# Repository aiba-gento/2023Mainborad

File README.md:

# 2023Mainborad
2023年ロボコン用マザーボード

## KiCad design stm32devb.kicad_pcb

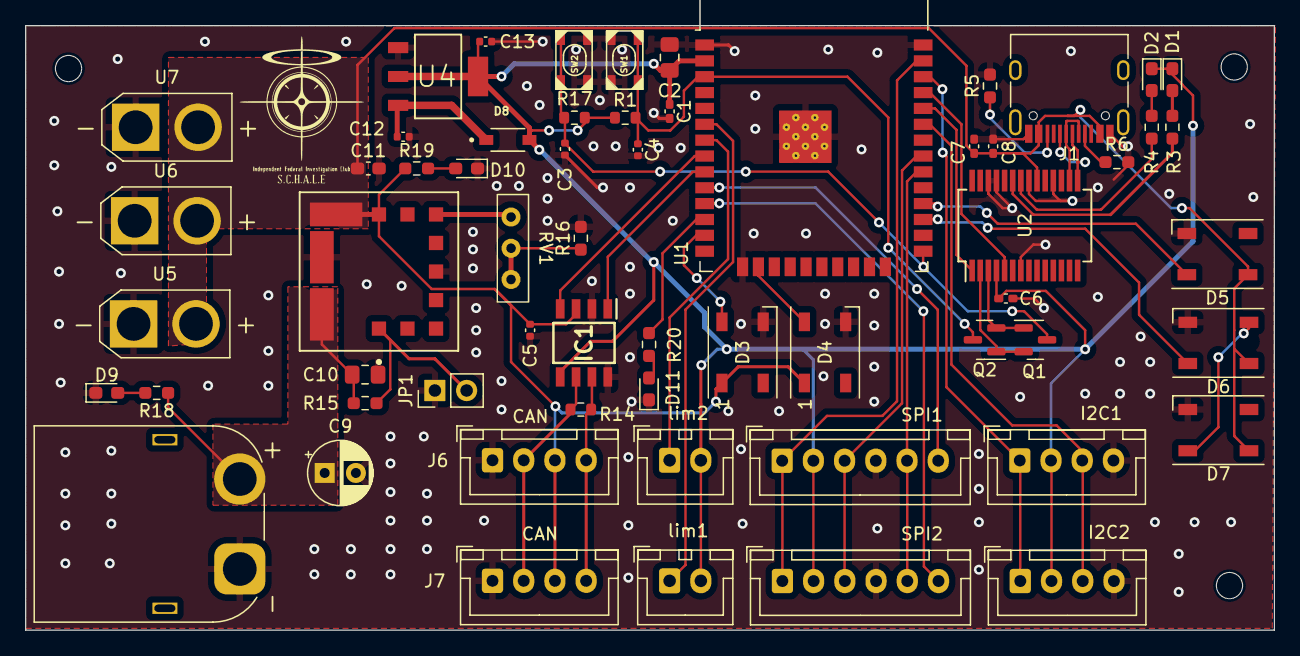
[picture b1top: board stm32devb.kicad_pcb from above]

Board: 2 copper layers, 100.0 x 48.4 mm, 60 parts (0 on the bottom side), 44 nets.

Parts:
C1, C6, C7: 0.1u; C_0402_1005Metric_Pad0.74x0.62mm_HandSolder
C2, C10: 22u; C_0805_2012Metric_Pad1.18x1.45mm_HandSolder
C3, C4, C5: 0.1u; C_0402_1005Metric
C8: 4.7u; C_0402_1005Metric_Pad0.74x0.62mm_HandSolder
C9: 220u; CP_Radial_D5.0mm_P2.50mm
C11: 10u; C_0603_1608Metric_Pad1.08x0.95mm_HandSolder
C12, C13: 1u; C_0402_1005Metric
D1, D2, D9, D10, D11: LED; LED_0603_1608Metric_Pad1.05x0.95mm_HandSolder
D3, D4, D5, D6, D7: WS2812B; LED_WS2812B_PLCC4_5.0x5.0mm_P3.2mm
D8: D; SS2040FL
IC1: TJA1441AT_0Z; SOIC127P600X175-8N
J1: USB_C_Receptacle_USB2.0; USB_C_Receptacle_HRO_TYPE-C-31-M-12
J2: SPI1; JST_XH_B6B-XH-A_1x06_P2.50mm_Vertical
J3: SPI2; JST_XH_B6B-XH-A_1x06_P2.50mm_Vertical
J4: I2C1; JST_XH_B4B-XH-A_1x04_P2.50mm_Vertical
J5: I2C2; JST_XH_B4B-XH-A_1x04_P2.50mm_Vertical
J6, J7: Conn_01x04; JST_XH_B4B-XH-A_1x04_P2.50mm_Vertical
J8, J9: Conn_01x02; JST_XH_B2B-XH-A_1x02_P2.50mm_Vertical
JP1: Jumper_2_Open; PinHeader_1x02_P2.54mm_Vertical
MD1: OKL-T/6-W12N-C; MURATA_OKL-T-6-W12N-C_0
Q1, Q2: BSS138; SOT-23
R1, R17: 10k; R_0603_1608Metric
R3, R4, R18, R19, R20: R; R_0603_1608Metric_Pad0.98x0.95mm_HandSolder
R5, R6: 4.7k; R_0603_1608Metric_Pad0.98x0.95mm_HandSolder
R14: 120; R_0603_1608Metric
R15: 20k; R_0603_1608Metric_Pad0.98x0.95mm_HandSolder
R16: 1.2k; R_0603_1608Metric_Pad0.98x0.95mm_HandSolder
RV1: 20k; TSR-3296
SW1: EN0; SKRPABE010
SW2: BOOT0; SKRPABE010
U1: ESP32-WROOM-32
U2: FT232RL; SSOP-28_5.3x10.2mm_P0.65mm
U3: XT60PW-M; AMASS_XT60PW-M_1x02_P7.20mm_Horizontal
U4: ADP3338AKCZ-3.3; SOT230P700X180-4N
U5, U6, U7: XT30PW-M; AMASS_XT30U-M_1x02_P5.0mm_Vertical

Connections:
+3.3V: C1.1, C2.1, C6.1, C13.1, D1.1 (K), D2.1 (K), D8.2 (A), IC1.5 (VIO), J2.2, J3.2, J4.2, J5.2, J8.2, J9.2, R1.1, R17.1, U1.2 (VDD), U2.4 (VCCIO), U4.2 (OUT)
+5V: C5.1, C7.1, C8.1, C11.1, D3.1 (VDD), D4.1 (VDD), D5.1 (VDD), D6.1 (VDD), D7.1 (VDD), IC1.3 (VCC), J1.A4 (VBUS), J1.A9 (VBUS), J1.B4 (VBUS), J1.B9 (VBUS), J6.3, J7.3, MD1.4 (VOUT), MD1.5 (SENSE), R19.1, U2.20 (VCC), U5.2 (+), U6.2 (+), U7.2 (+)
+BATT: C9.1, C10.1, MD1.2 (VIN), R15.1, R18.1, U3.2
BLEStateRGB: D3.4 (DIN), U1.13 (IO14)
BOOT0: C3.1, Q1.3 (D), R17.2, SW2.2, U1.25 (IO0)
CANH: IC1.7 (CANH), J6.4, J7.4, R14.1
CANL: IC1.6 (CANL), J6.2, J7.2, R14.2
CANRX: IC1.1 (TXD), U1.9 (IO33)
CANTX: IC1.4 (RXD), U1.8 (IO32)
DTR0: Q1.2 (S), Q2.1 (G), U2.2 (DTR)
EN0: C4.1, Q2.3 (D), R1.2, SW1.2, U1.3 (EN)
GND: C1.2, C2.2, C3.2, C4.2, C5.2, C6.2, C7.2, C8.2, C9.2, C10.2, C11.2, C12.2, C13.2, D3.3 (VSS), D4.3 (VSS), D5.3 (VSS), D6.3 (VSS), D7.3 (VSS), D9.1 (K), D10.1 (K), D11.1 (K), IC1.2 (GND), IC1.8 (S), J1.A1 (GND), J1.A12 (GND), J1.B1 (GND), J1.B12 (GND), J2.4, J3.4, J4.4, J5.4, J6.1, J7.1, JP1.1 (A), MD1.3 (1_GROUND), MD1.7 (2_GROUND), R5.2, R6.2, R16.2, SW1.1, SW2.1, U1.1 (GND), U1.15 (GND), U1.38 (GND), U1.39 (GND), U2.7 (GND), U2.18 (GND), U2.21 (GND), U2.25 (AGND), U2.26 (TEST), U3.1, U4.1 (GND), U5.1 (-), U6.1 (-), U7.1 (-)
MISO: J2.3, J3.3, U1.31 (IO19)
MOSI: J2.1, J3.1, U1.37 (IO23)
unnamed: D1.2 (A), R3.1
unnamed: D2.2 (A), R4.1
unnamed: D6.2 (DOUT), D7.4 (DIN)
unnamed: D9.2 (A), R18.2
unnamed: D10.2 (A), R19.2
unnamed: D11.2 (A), R20.2
unnamed: J1.A5 (CC1), R6.1
unnamed: J1.B5 (CC2), R5.1
unnamed: JP1.2 (B), MD1.1 (~ON~{/OFF_CONTROL), R15.2
unnamed: MD1.6 (TRIM), RV1.1
unnamed: R16.1, RV1.2, RV1.3
unnamed: R3.2, U2.23 (CBUS0)
unnamed: R4.2, U2.22 (CBUS1)
RGB1: D5.4 (DIN), U1.28 (IO17)
RGB2: D6.4 (DIN), U1.27 (IO16)
RTS0: Q1.1 (G), Q2.2 (S), U2.3 (RTS)
RX0: U1.34 (RXD0/IO3), U2.1 (TXD)
SCL: J4.1, J5.1, U1.36 (IO22)
SCLK: J2.5, J3.5, U1.30 (IO18)
SDA: J4.3, J5.3, U1.33 (IO21)
SPIState: D4.4 (DIN), U1.16 (IO13)
SS1: J2.6, U1.10 (IO25)
SS2: J3.6, U1.11 (IO26)
TX0: U1.35 (TXD0/IO1), U2.5 (RXD)
USB0D+: J1.A6 (D+), J1.B6 (D+), U2.15 (USBD+)
USB0D-: J1.A7 (D-), J1.B7 (D-), U2.16 (USBD-)
VCC: C12.1, D8.1 (K), U4.3 (IN)
led1: R20.1, U1.12 (IO27)
lim1: J8.1, U1.6 (IO34)
lim2: J9.1, U1.7 (IO35)

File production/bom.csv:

Designator,Footprint,Quantity,Value,LCSC Part #
"C1, C3, C4, C5, C6, C7",0402,6,0.1u,
"C10, C2",0805,2,22u,
C11,0603,1,10u,
"C12, C13",0402,2,1u,
C8,0402,1,4.7u,
C9,CP_Radial_D5.0mm_P2.50mm,1,220u,
"D1, D10, D11, D2, D9",0603,5,LED,
"D3, D4, D5, D6, D7",LED_WS2812B_PLCC4_5.0x5.0mm_P3.2mm,5,WS2812B,
D8,SS2040FL,1,D,
IC1,SOIC127P600X175-8N,1,TJA1441AT_0Z,
J1,USB_C_Receptacle_HRO_TYPE-C-31-M-12,1,USB_C_Receptacle_USB2.0,
J2,JST_XH_B6B-XH-A_1x06_P2.50mm_Vertical,1,SPI1,
J3,JST_XH_B6B-XH-A_1x06_P2.50mm_Vertical,1,SPI2,
J4,JST_XH_B4B-XH-A_1x04_P2.50mm_Vertical,1,I2C1,
J5,JST_XH_B4B-XH-A_1x04_P2.50mm_Vertical,1,I2C2,
"J6, J7",JST_XH_B4B-XH-A_1x04_P2.50mm_Vertical,2,Conn_01x04,
"J8, J9",JST_XH_B2B-XH-A_1x02_P2.50mm_Vertical,2,Conn_01x02,
JP1,PinHeader_1x02_P2.54mm_Vertical,1,Jumper_2_Open,
MD1,MURATA_OKL-T-6-W12N-C_0,1,OKL-T/6-W12N-C,OKL-T/6-W12N-C
"Q1, Q2",SOT-23,2,BSS138,
"R1, R17",0603,2,10k,
R14,0603,1,120,
R15,0603,1,20k,
R16,0603,1,1.2k,
"R18, R19, R20, R3, R4",0603,5,R,
"R5, R6",0603,2,4.7k,
RV1,TSR-3296,1,20k,
SW1,SKRPABE010,1,EN0,
SW2,SKRPABE010,1,BOOT0,
U1,ESP32-WROOM-32,1,ESP32-WROOM-32,
U2,SSOP-28_5.3x10.2mm_P0.65mm,1,FT232RL,
U3,AMASS_XT60PW-M_1x02_P7.20mm_Horizontal,1,XT60PW-M,
U4,SOT230P700X180-4N,1,ADP3338AKCZ-3.3,ADP3338AKCZ-3.3
"U5, U6, U7",AMASS_XT30U-M_1x02_P5.0mm_Vertical,3,XT30PW-M,

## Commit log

2023-08-14 init commit
2023-08-15 ENのコンデンサーを1uFにしました
    自動起動と自動書き込みの為です。
    今回実装した抵抗器の値を入れておきました
